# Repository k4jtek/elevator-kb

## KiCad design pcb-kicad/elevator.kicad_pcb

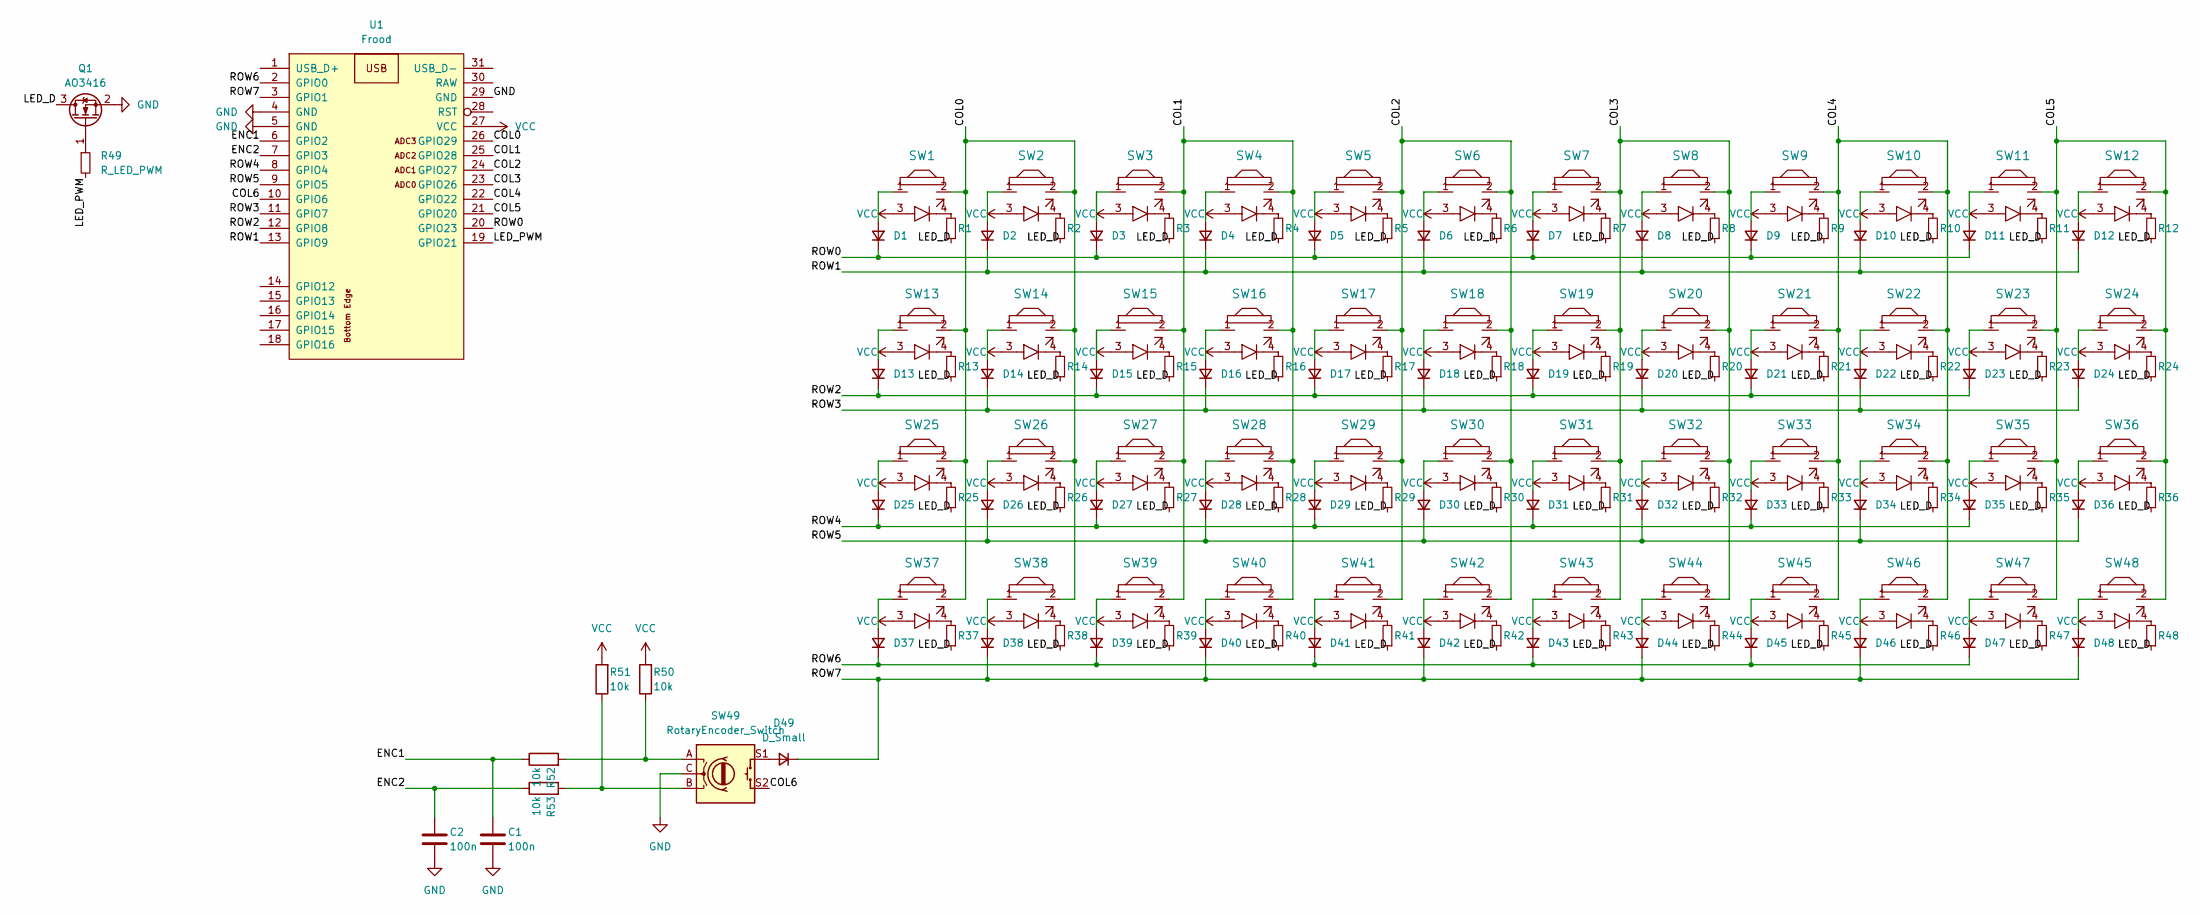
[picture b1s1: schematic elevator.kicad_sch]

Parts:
C1, C2: 100n; C_Disc_D4.3mm_W1.9mm_P5.00mm
D1, D2, D3, D4, D5, D6, D7, D8, D9, D10, D11, D12, D13, D14, D15, D16, D17, D18, D19, D20, D21, D22, D23, D24, D25, D26, D27, D28, D29, D30, D31, D32, D33, D34, D35, D36, D37, D38, D39, D40, D41, D42, D43, D44, D45, D46, D47, D48: D_SW; Diode-dual
D49: D_Small; Diode-dual
Q1: AO3416; SOT-23
R1, R2, R3, R4, R5, R6, R7, R8, R9, R10, R11, R12, R13, R14, R15, R16, R17, R18, R19, R20, R21, R22, R23, R24, R25, R26, R27, R28, R29, R30, R31, R32, R33, R34, R35, R36, R37, R38, R39, R40, R41, R42, R43, R44, R45, R46, R47, R48: R_LED; Resistor-Hybrid
R49: R_LED_PWM; Resistor-Hybrid
R50, R51, R52, R53: 10k; Resistor-Hybrid
SW1, SW2, SW3, SW4, SW5, SW6, SW7, SW8, SW9, SW10, SW11, SW12, SW13, SW14, SW15, SW16, SW17, SW18, SW19, SW20, SW21, SW22, SW23, SW24, SW25, SW26, SW27, SW28, SW29, SW30, SW31, SW32, SW33, SW34, SW35, SW36, SW37, SW38, SW39, SW40, SW41, SW42, SW43, SW44, SW45, SW46, SW47, SW48: MX-with-LED; MX-Alps-Choc-1U
SW49: RotaryEncoder_Switch; RotaryEncoder_Alps_EC11E-Switch_Vertical_H20mm
U1: Frood; Frood_PinHeader_2x13+5_P2.54mm_Labels_Top

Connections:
/COL0: SW1.2, SW2.2, SW13.2, SW14.2, SW25.2, SW26.2, SW37.2, SW38.2, U1.26 (GPIO29)
/COL1: SW3.2, SW4.2, SW15.2, SW16.2, SW27.2, SW28.2, SW39.2, SW40.2, U1.25 (GPIO28)
/COL2: SW5.2, SW6.2, SW17.2, SW18.2, SW29.2, SW30.2, SW41.2, SW42.2, U1.24 (GPIO27)
/COL3: SW7.2, SW8.2, SW19.2, SW20.2, SW31.2, SW32.2, SW43.2, SW44.2, U1.23 (GPIO26)
/COL4: SW9.2, SW10.2, SW21.2, SW22.2, SW33.2, SW34.2, SW45.2, SW46.2, U1.22 (GPIO22)
/COL5: SW11.2, SW12.2, SW23.2, SW24.2, SW35.2, SW36.2, SW47.2, SW48.2, U1.21 (GPIO20)
/COL6: SW49.S2, U1.10 (GPIO6)
/ENC1: C1.1, R52.1, U1.6 (GPIO2)
/ENC2: C2.1, R53.1, U1.7 (GPIO3)
/LED_D: Q1.3 (D), R1.1, R2.1, R3.1, R4.1, R5.1, R6.1, R7.1, R8.1, R9.1, R10.1, R11.1, R12.1, R13.1, R14.1, R15.1, R16.1, R17.1, R18.1, R19.1, R20.1, R21.1, R22.1, R23.1, R24.1, R25.1, R26.1, R27.1, R28.1, R29.1, R30.1, R31.1, R32.1, R33.1, R34.1, R35.1, R36.1, R37.1, R38.1, R39.1, R40.1, R41.1, R42.1, R43.1, R44.1, R45.1, R46.1, R47.1, R48.1
/LED_PWM: R49.2, U1.19 (GPIO21)
/ROW0: D1.1 (K), D3.1 (K), D5.1 (K), D7.1 (K), D9.1 (K), D11.1 (K), U1.20 (GPIO23)
/ROW1: D2.1 (K), D4.1 (K), D6.1 (K), D8.1 (K), D10.1 (K), D12.1 (K), U1.13 (GPIO9)
/ROW2: D13.1 (K), D15.1 (K), D17.1 (K), D19.1 (K), D21.1 (K), D23.1 (K), U1.12 (GPIO8)
/ROW3: D14.1 (K), D16.1 (K), D18.1 (K), D20.1 (K), D22.1 (K), D24.1 (K), U1.11 (GPIO7)
/ROW4: D25.1 (K), D27.1 (K), D29.1 (K), D31.1 (K), D33.1 (K), D35.1 (K), U1.8 (GPIO4)
/ROW5: D26.1 (K), D28.1 (K), D30.1 (K), D32.1 (K), D34.1 (K), D36.1 (K), U1.9 (GPIO5)
/ROW6: D37.1 (K), D39.1 (K), D41.1 (K), D43.1 (K), D45.1 (K), D47.1 (K), U1.2 (GPIO0)
/ROW7: D38.1 (K), D40.1 (K), D42.1 (K), D44.1 (K), D46.1 (K), D48.1 (K), D49.1 (K), U1.3 (GPIO1)
GND: C1.2, C2.2, Q1.2 (S), SW49.C, U1.4 (GND), U1.5 (GND), U1.29 (GND)
unnamed: D1.2 (A), SW1.1
unnamed: D2.2 (A), SW2.1
unnamed: D3.2 (A), SW3.1
unnamed: D4.2 (A), SW4.1
unnamed: D5.2 (A), SW5.1
unnamed: D6.2 (A), SW6.1
unnamed: D7.2 (A), SW7.1
unnamed: D8.2 (A), SW8.1
unnamed: D9.2 (A), SW9.1
unnamed: D10.2 (A), SW10.1
unnamed: D11.2 (A), SW11.1
unnamed: D12.2 (A), SW12.1
unnamed: D13.2 (A), SW13.1
unnamed: D14.2 (A), SW14.1
unnamed: D15.2 (A), SW15.1
unnamed: D16.2 (A), SW16.1
unnamed: D17.2 (A), SW17.1
unnamed: D18.2 (A), SW18.1
unnamed: D19.2 (A), SW19.1
unnamed: D20.2 (A), SW20.1
unnamed: D21.2 (A), SW21.1
unnamed: D22.2 (A), SW22.1
unnamed: D23.2 (A), SW23.1
unnamed: D24.2 (A), SW24.1
unnamed: D25.2 (A), SW25.1
unnamed: D26.2 (A), SW26.1
unnamed: D27.2 (A), SW27.1
unnamed: D28.2 (A), SW28.1
unnamed: D29.2 (A), SW29.1
unnamed: D30.2 (A), SW30.1
unnamed: D31.2 (A), SW31.1
unnamed: D32.2 (A), SW32.1
unnamed: D33.2 (A), SW33.1
unnamed: D34.2 (A), SW34.1
unnamed: D35.2 (A), SW35.1
unnamed: D36.2 (A), SW36.1
unnamed: D37.2 (A), SW37.1
unnamed: D38.2 (A), SW38.1
unnamed: D39.2 (A), SW39.1
unnamed: D40.2 (A), SW40.1
unnamed: D41.2 (A), SW41.1
unnamed: D42.2 (A), SW42.1
unnamed: D43.2 (A), SW43.1
unnamed: D44.2 (A), SW44.1
unnamed: D45.2 (A), SW45.1
unnamed: D46.2 (A), SW46.1
unnamed: D47.2 (A), SW47.1
unnamed: D48.2 (A), SW48.1
unnamed: D49.2 (A), SW49.S1
unnamed: Q1.1 (G), R49.1
unnamed: R1.2, SW1.4
unnamed: R2.2, SW2.4
unnamed: R3.2, SW3.4
unnamed: R4.2, SW4.4
unnamed: R5.2, SW5.4
unnamed: R6.2, SW6.4
unnamed: R7.2, SW7.4
unnamed: R8.2, SW8.4
unnamed: R9.2, SW9.4
unnamed: R10.2, SW10.4
unnamed: R11.2, SW11.4
unnamed: R12.2, SW12.4
unnamed: R13.2, SW13.4
unnamed: R14.2, SW14.4
unnamed: R15.2, SW15.4
unnamed: R16.2, SW16.4
unnamed: R17.2, SW17.4
unnamed: R18.2, SW18.4
unnamed: R19.2, SW19.4
unnamed: R20.2, SW20.4
unnamed: R21.2, SW21.4
unnamed: R22.2, SW22.4
unnamed: R23.2, SW23.4
unnamed: R24.2, SW24.4
unnamed: R25.2, SW25.4
unnamed: R26.2, SW26.4
unnamed: R27.2, SW27.4
unnamed: R28.2, SW28.4
unnamed: R29.2, SW29.4
unnamed: R30.2, SW30.4
unnamed: R31.2, SW31.4
unnamed: R32.2, SW32.4
unnamed: R33.2, SW33.4
unnamed: R34.2, SW34.4
unnamed: R35.2, SW35.4
unnamed: R36.2, SW36.4
unnamed: R37.2, SW37.4
unnamed: R38.2, SW38.4
unnamed: R39.2, SW39.4
unnamed: R40.2, SW40.4
unnamed: R41.2, SW41.4
unnamed: R42.2, SW42.4
unnamed: R43.2, SW43.4
unnamed: R44.2, SW44.4
unnamed: R45.2, SW45.4
unnamed: R46.2, SW46.4
unnamed: R47.2, SW47.4
unnamed: R48.2, SW48.4
unnamed: R50.1, R52.2, SW49.A
unnamed: R51.1, R53.2, SW49.B
VCC: R50.2, R51.2, SW1.3, SW2.3, SW3.3, SW4.3, SW5.3, SW6.3, SW7.3, SW8.3, SW9.3, SW10.3, SW11.3, SW12.3, SW13.3, SW14.3, SW15.3, SW16.3, SW17.3, SW18.3, SW19.3, SW20.3, SW21.3, SW22.3, SW23.3, SW24.3, SW25.3, SW26.3, SW27.3, SW28.3, SW29.3, SW30.3, SW31.3, SW32.3, SW33.3, SW34.3, SW35.3, SW36.3, SW37.3, SW38.3, SW39.3, SW40.3, SW41.3, SW42.3, SW43.3, SW44.3, SW45.3, SW46.3, SW47.3, SW48.3, U1.27 (VCC)

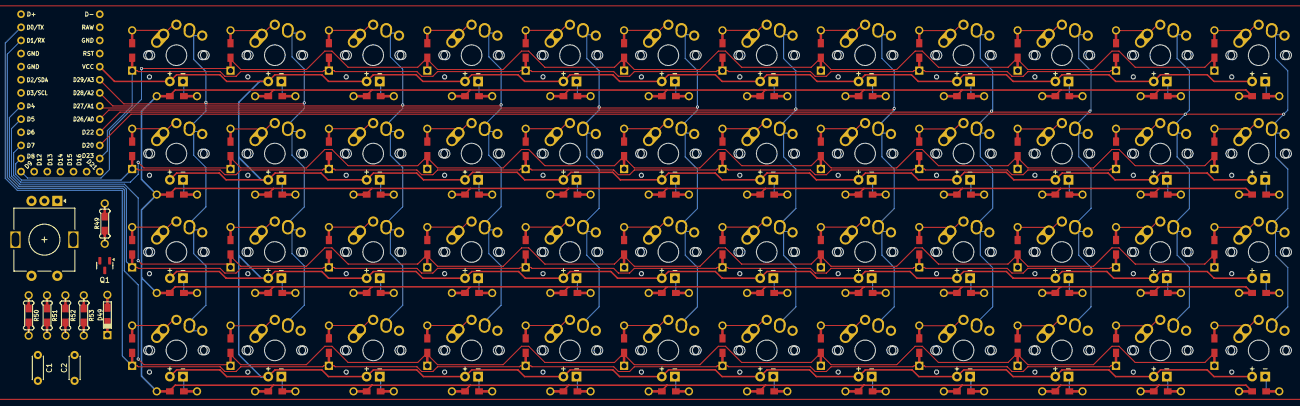
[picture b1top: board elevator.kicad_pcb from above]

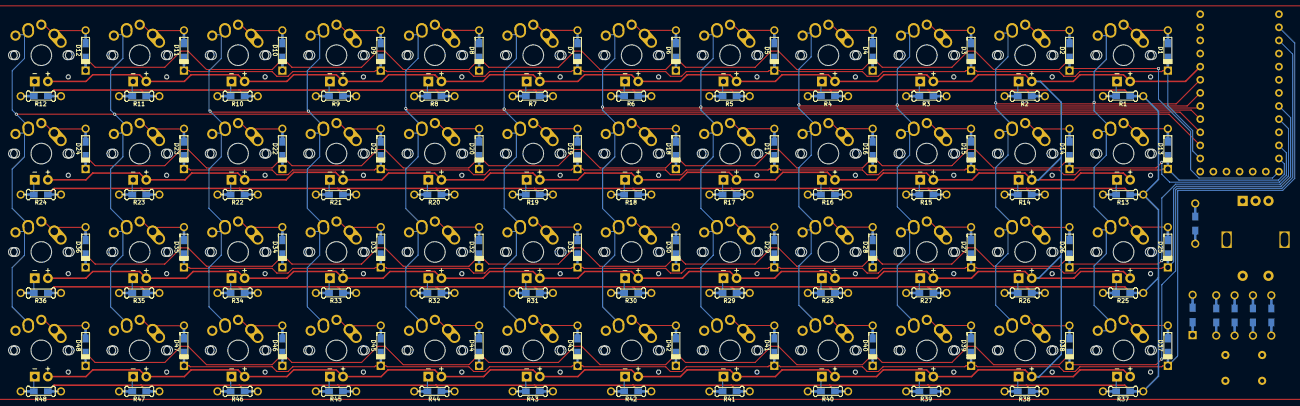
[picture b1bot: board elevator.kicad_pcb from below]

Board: 2 copper layers, 155 parts (96 on the bottom side), 121 nets.

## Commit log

2024-02-26 Init KiCad project
2024-02-26 Add kicad libraries
2024-02-27 Draw switch matrix on the schematic
2024-02-28 Update schematic
2024-03-01 Change schematic a bit and update PCB
2024-03-06 Route switch matrix and couple other things
2024-03-08 Route LEDs
2024-03-08 Finish LED routing, route columns to the controller
2024-03-14 Minor changes
2024-03-14 Some wirint, add fp-lib-table to .gitignore
2024-03-15 Finish matrix wiring, add encoder schematic
2024-03-17 Change VCC and GND labels for power symbols
2024-03-18 Add rotary encoder circuitry to the PCB
2024-03-18 Add ledstrip circuitry to schematic
